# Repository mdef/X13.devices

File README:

The X13.Home project, http://X13Home.org, http://x13home.github.io

X13.devices
===========

Firmware section for project X13.Home

Automation System oriented to "Smart House" over MQTT(SN) protocol

devices     - firmware for Arduino nano (atmega328) nodes and host

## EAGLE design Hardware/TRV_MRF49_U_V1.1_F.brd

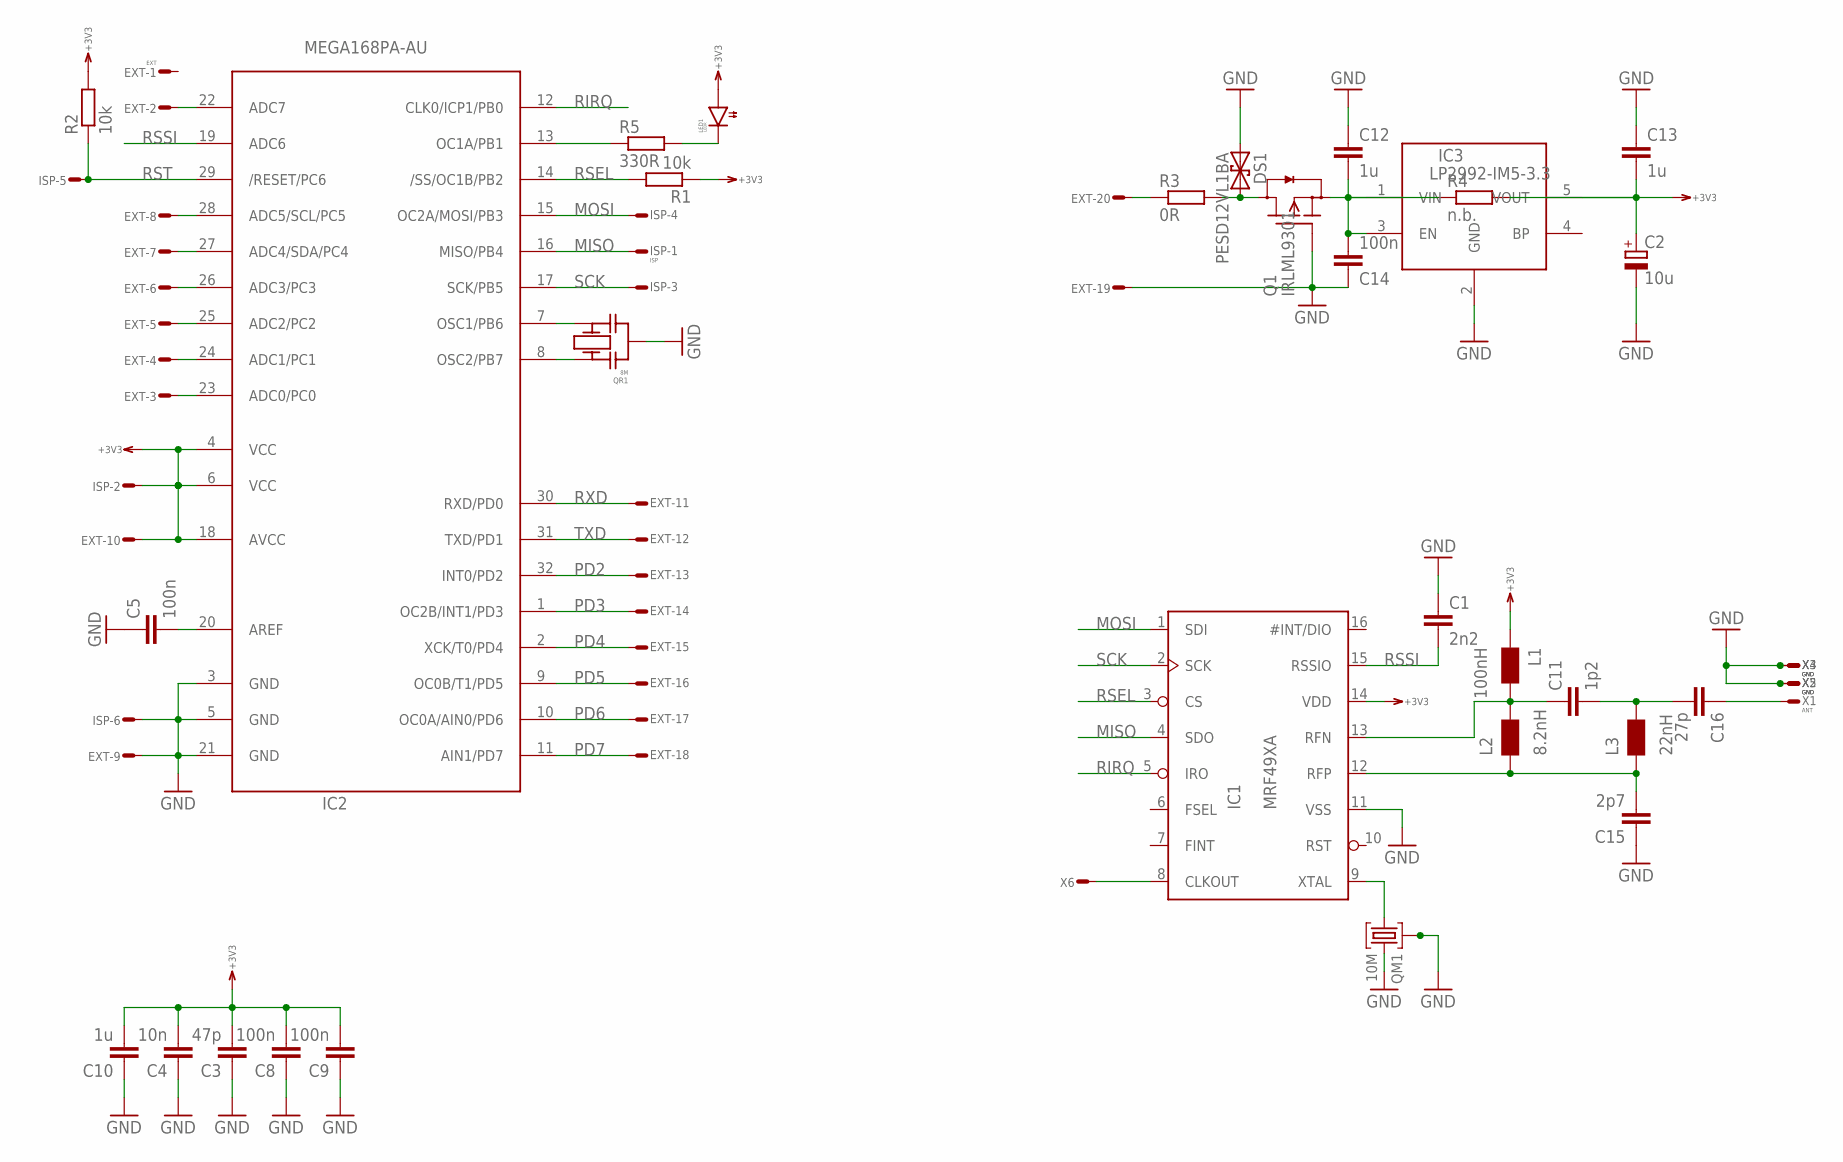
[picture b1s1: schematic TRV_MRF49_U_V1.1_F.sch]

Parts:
C1: 2n2; 0603
C2: 10u; SMC_B
C3: 47p; 0603
C4: 10n; 0603
C5, C8, C9, C14: 100n; 0603
C10, C12, C13: 1u; 0603
C11: 1p2; 0603
C15: 2p7; 0603
C16: 27p; 0603
DS1: PESD12VL1BA; SOD323
EXT: EXT; ML20
IC1: MRF49XA; TSSOP16
IC2: MEGA168PA-AU; TQFP32-08
IC3: LP2992-IM5-3.3; SOT23-5
ISP: ISP; ML6
L1: 100nH; 0603
L2: 8.2nH; 0603
L3: 22nH; 0603
LED1: LEDR; 0603
Q1: IRLML9301; SOT23
QM1: 10M; ABM3C
QR1: 8M; CR
R1, R2: 10k; 0603
R3: 0R; 0603
R4: n.b.; 0603
R5: 330R; 0603
X1: ANT; S2.54/1.27
X2, X3, X4, X5: GND; S2.54/1.27
X6: WIREPADR; S1.27R

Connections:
+3V3: C2.+, C3.2, C4.2, C8.2, C9.2, C10.2, C13.2, EXT.10, IC1.14 (VDD), IC2.4 (VCC), IC2.6 (VCC), IC2.18 (AVCC), IC3.5 (VOUT), ISP.2, L1.1, LED1.1 (A), R1.1, R2.2, R4.2
GND: C1.1, C2.-, C3.1, C4.1, C5.1, C8.1, C9.1, C10.1, C12.1, C13.1, C14.1, C15.1, DS1.A (1), EXT.9, EXT.19, IC1.11 (VSS), IC2.3 (GND), IC2.5 (GND), IC2.21 (GND), IC3.2 (GND), ISP.6, Q1.1 (G), QM1.P$2 (M1), QM1.P$3 (2), QM1.P$4 (M2), QR1.M, X2.1, X3.1, X4.1, X5.1
MISO: IC1.4 (SDO), IC2.16 (MISO/PB4), ISP.1
MOSI: IC1.1 (SDI), IC2.15 (OC2A/MOSI/PB3), ISP.4
unnamed: IC1.8 (CLKOUT), X6.1
unnamed: C11.2, C16.2, L3.2
unnamed: EXT.2, IC2.22 (ADC7)
unnamed: IC1.9 (XTAL), QM1.P$1 (1)
unnamed: DS1.C (2), Q1.3 (D), R3.2
unnamed: C5.2, IC2.20 (AREF)
unnamed: IC2.8 (OSC2/PB7), QR1.1
unnamed: IC2.7 (OSC1/PB6), QR1.2
unnamed: EXT.20, R3.1
unnamed: IC2.13 (OC1A/PB1), R5.1
unnamed: C12.2, C14.2, IC3.1 (VIN), IC3.3 (EN), Q1.2 (S), R4.1
unnamed: C11.1, IC1.13 (RFN), L1.2, L2.2
unnamed: LED1.2 (C), R5.2
unnamed: C15.2, IC1.12 (RFP), L2.1, L3.1
unnamed: C16.1, X1.1
PC0: EXT.3, IC2.23 (ADC0/PC0)
PC1: EXT.4, IC2.24 (ADC1/PC1)
PC2: EXT.5, IC2.25 (ADC2/PC2)
PC3: EXT.6, IC2.26 (ADC3/PC3)
PC4: EXT.7, IC2.27 (ADC4/SDA/PC4)
PC5: EXT.8, IC2.28 (ADC5/SCL/PC5)
PD2: EXT.13, IC2.32 (INT0/PD2)
PD3: EXT.14, IC2.1 (OC2B/INT1/PD3)
PD4: EXT.15, IC2.2 (XCK/T0/PD4)
PD5: EXT.16, IC2.9 (OC0B/T1/PD5)
PD6: EXT.17, IC2.10 (OC0A/AIN0/PD6)
PD7: EXT.18, IC2.11 (AIN1/PD7)
RIRQ: IC1.5 (IRO), IC2.12 (CLK0/ICP1/PB0)
RSEL: IC1.3 (CS), IC2.14 (/SS/OC1B/PB2), R1.2
RSSI: C1.2, IC1.15 (RSSIO), IC2.19 (ADC6)
RST: IC2.29 (/RESET/PC6), ISP.5, R2.1
RXD: EXT.11, IC2.30 (RXD/PD0)
SCK: IC1.2 (SCK), IC2.17 (SCK/PB5), ISP.3
TXD: EXT.12, IC2.31 (TXD/PD1)

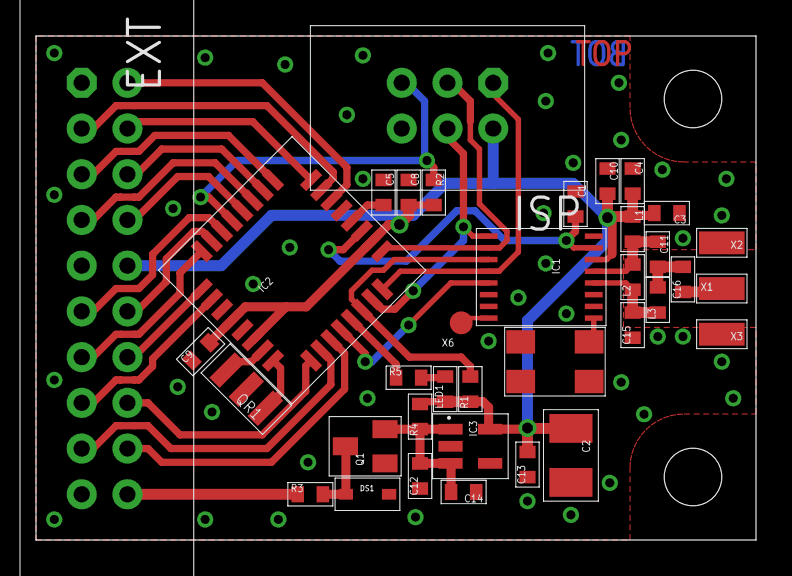
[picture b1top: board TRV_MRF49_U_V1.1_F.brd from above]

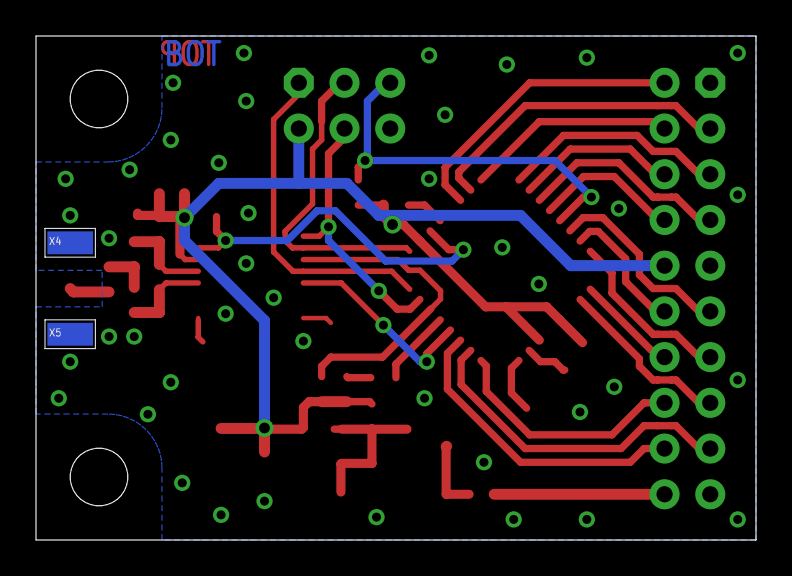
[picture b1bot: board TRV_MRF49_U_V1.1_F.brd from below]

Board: 2 copper layers, 40.0 x 28.0 mm, 38 parts (2 on the bottom side), 38 nets.

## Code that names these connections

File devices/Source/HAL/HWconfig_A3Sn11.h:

/*
Copyright (c) 2011-2014 <comparator@gmx.de>

This file is part of the X13.Home project.
http://X13home.org
http://X13home.net
http://X13home.github.io/

BSD New License
See LICENSE file for license details.
*/

#ifndef HWCONFIG_A3SN11_H
#define HWCONFIG_A3SN11_H

// Busware CSM V2.0
// uc ATMega1284p
// PHY: UART

// PORTA
// PA0  --    LEDG
// PA1  --    LEDR
// PA2  --    R-CFG1.1
// PA3  --    R-CFG1.2
// PA4  CN9
// PA5  CN8
// PA6  --
// PA7  --
// PORTB
// PB0  CN30
// PB1  CN22  RF_IRQ
// PB2  CN24
// PB3  CN25
// PB4  --    RF_NCS
// PB5  CN28  RF_MOSI
// PB6  CN27  RF_MISO
// PB7  CN29  RF_SCK
// PORTC
// PC0  CN15  SCL
// PC1  CN14  SDA
// PC2  CN13  JTAG_TCK
// PC3  CN11  JTAG_TMS
// PC4  CN10  JTAG_TDO
// PC5  CN12  JTAG_TDI
// PC6  --
// PC7  --
// PORTD
// PD0  CN3   RXD0
// PD1  CN4   TXD0
// PD2  CN23  RF_GDO2/Not Used
// PD3  CN6
// PD4  CN7
// PD5  --    R-CFG2
// PD6  --    R-CFG3
// PD7  --

#include <avr/io.h>
#include <avr/eeprom.h>
//#include <util/delay.h>

#include "../../FreeRTOS/include/FreeRTOS.h"
#include "../../FreeRTOS/include/task.h"
#include "../../FreeRTOS/include/queue.h"
#include "../../FreeRTOS/include/semphr.h"

#define INIT_SYSTEM()

// DIO Section
#define DIO_PORT_SIZE               8
#define EXTDIO_MAXPORT_NR           4                                     // Number of digital Ports
#define PORTNUM_2_PORT              {(uint16_t)&PORTA, (uint16_t)&PORTB, (uint16_t)&PORTC, (uint16_t)&PORTD}
#define PORTNUM_2_MASK              {(uint8_t)0x00, (uint8_t)0x00, (uint8_t)0x00, (uint8_t)0x00}
// End DIO Section

// UART Section
#define UART_PORT                   PORTD
#define UART_DDR                    DDRD
#define UART_RX_PIN                 PD0
#define UART_TX_PIN                 PD1
#define UART_RX_DATA                UDR0
#define UART_TX_DATA                UDR0

#define UART_TX_DISABLE_INT()       UCSR0B &= ~(1<<UDRIE0)
#define UART_TX_ENABLE_INT()        UCSR0B |= (1<<UDRIE0)
// End UART Section

#define UART_PHY                    1
#define RF_NODE                     1

#define PHY1_ADDR_t                 uint8_t
#define RF_ADDR_t                   uint8_t
#define ADDR_BROADCAST_PHY1         (PHY1_ADDR_t)0x00
#define ADDR_UNDEF_PHY1             (PHY1_ADDR_t)0xFF
#define ADDR_DEFAULT_RF             (RF_ADDR_t)0x04
#define ADDR_UNDEF_RF               (RF_ADDR_t)0xFF

// Object's Dictionary Section
#define OD_DEV_UC_TYPE              'A'
#define OD_DEV_UC_SUBTYPE           '3'
#define OD_DEV_PHY1                 'S'
#define OD_DEV_PHY2                 'n'
#define OD_DEV_HW_TYP_H             '1'
#define OD_DEV_HW_TYP_L             '1'

#define OD_ADDR_TYPE                objUInt8

#include "../PHY/UART/uart_phy.h"

#define PHY1_Init                   UART_Init
#define PHY1_Send                   UART_Send
#define PHY1_Get                    UART_Get
#define PHY1_NodeId                 objRFNodeId
#define PHY1_GateId                 objGateID
#define UART_ADDR                   phy1
#define UART_ADDR_t                 uint8_t

#define eeprom_init_hw()
#define eeprom_read(pBuf, Addr, Len)  eeprom_read_block((void *)pBuf, (const void *)Addr, (size_t)Len)
#define eeprom_write(pBuf, Addr, Len) eeprom_write_block((const void *)pBuf, (void *)Addr, (size_t)Len)

#endif // HWCONFIG_A3SN11_H

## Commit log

2012-12-31 Public Version.
2012-12-31 Added PDF View
2013-01-05 Development version
2013-01-06 MQTTS.c removed misunderstandings and typing errors extser.c restored delete subroutine
2013-01-21 TWI API changed
2013-01-21 deleted hardware
2013-01-21 New TWI API
2013-01-23 LM75 Prototype
2013-01-29 Merged
2013-02-04 Hih61xx driver untested
2013-02-07 New I2C API, small UART RX changes.
2013-02-07 Version 2.3
2013-02-08 Start OWI
2013-02-08 Start OWI development
2013-02-09 RFM12 aggressive pool method
2013-02-09 Object dictionary changes
2013-02-09 BMP085 Test
2013-02-10 RF aggressive pool method
2013-02-10 Version 2.3a
2013-02-17 Added TWI Bus Status and Watchdog
2013-02-18 TWI Bugfix version
2013-02-19 TWIM Watchdog Version 1.2
2013-02-19 TWI Watchdog
2013-02-20 TWI WatchDog Vers 3
2013-02-21 TWI Watchdog and startup bugfix
2013-02-21 Version 2.4
2013-02-22 Test TWIM WD
2013-02-23 Packed Objects
2013-02-25 Vers 2.4.0
2013-02-25 Version 2.4.0
2013-02-27 Vers 2.4.1
2013-03-01 NOT Working Develop version
2013-03-03 Vers 2.4.2
2013-03-09 Version 2.4.2
2013-03-17 Added Proto Si114x
2013-03-19 Added PROTO RFM23
2013-04-01 LAN Test Version
2013-04-01 Test Version ARP + ICMP + DHCP
2013-04-02 Test3
2013-04-02 Added Node Don't Work
2013-04-02 deleted addr
2013-04-02 little bit
2013-04-03 Alfa Version
2013-04-04 Version 2.5.Alfa
2013-04-04 Alfa 2
2013-04-04 Changed Predefined ID's
2013-04-04 Switch to LAN_RF Added RFM12
2013-04-05 Alfa2
2013-04-05 Alfa 3, LAN Bugfix
2013-04-05 Alfa 4 Version Added PHY's RF - RFM12, configurations UNODE & JNODE
2013-04-05 Alfa 5, Added PHY - CC11xx
2013-04-05 typo
2013-04-14 Optimization
2013-04-15 Changed MQTT and PHY API
2013-04-19 Added PROTO W5100
2013-05-10 Merged RF and LAN Sources
2013-05-10 Proto Version 2.5.0 RF_GATEWAY DON'T WORK
2013-05-11 Gateway don't work
2013-05-11 Added LED LAN Activity Corrected UART-GW API
2013-05-12 Gateway Test Version
2013-05-13 Version 2.5.0.beta1
2013-05-13 RF-GW BugFix
2013-05-14 Compiled with AVR Studio 6.1
2013-05-20 Added panSTamp USE_RTC_OSC = 1
2013-05-21 Version 2.4.3 - Compatibility with Develop version
2013-05-22 Added HEX Files
2013-05-22 Changed MQTTS Proc's Publish, Subscribe, Register Changed Analog inputs configuration Changed RF_USE_RSSI Temporarely unused Added TWI Callback Functions
2013-05-23 Build 2.5.1.b1
2013-05-23 Added HEXs
2013-05-24 Test VArs
2013-05-28 Changed RF API, GW Don't Work !!
2013-05-31 Gateway Work Version
2013-06-04 Si7005 Revision B.
2013-06-05 Version 2.5.2 RC
2013-06-11 Fixed Si7005 Errors
2013-06-14 Change list updated
2013-06-20 Changed Plugins structure
2013-06-25 Added DummyGW device - Gateway w/o RF Interface
2013-06-26 Added BlinkM Prototype
2013-06-27 BlinkM, Pool Version, !! Not Tested
2013-06-27 BlinkM driver work with bus planer.
2013-06-28 Bugfix, Digital IO 19, Added BlinkM TWI Driver, Added Data type Int64
2013-06-30 Added WIZNET prototype
2013-06-30 Added W5200 Register description
2013-07-04 Wiznet HAL
2013-07-20 Wiznet Modi
2013-07-21 Wiznet Added Socket Proto
2013-08-21 Optimize structure
2013-09-04 Added uNode V2.0
2013-09-08 Version 2.5.5 Release Candidate
2013-09-12 Build 2.5.5 RC
2013-10-17 BugFix, Node ADDR = 0xC0 | 0xDB
2013-10-24 BugFix, not stable detection TWI devices
2013-10-25 Updates HEXs
2013-10-30 Readme copy/paste error.
2013-11-11 Added Dummy ATMega256
2013-11-11 Release Version 2.6.0
2013-11-11 Release
2013-11-11 Typo correction
2013-11-12 Added Arduino LAN 16M
2013-11-22 Added TWI Driver CCd2xx[S]
2013-11-28 Added SHT21 proto changed TWI arbitration structure.
2013-11-29 Added TWI Driver MCP23016 Added TWI Driver SHT21 Changed TWI Arbitration
2013-12-01 Connected tested TWI drivers
2013-12-03 Optimized TWI Drivers LM75 and BMP180 Deleted SI7005
2013-12-19 Added Arduino NANO prototype
2014-01-08 Bugfix eeprom.c progmemReadOD fault output state
2014-01-23 Added VERSION
2014-01-28 ExtAI + ExtPWM without PRR
2014-01-30 Don't work
2014-01-30 Added dubug to mqtts
2014-01-30 Tests 2,3,5 Failed
2014-02-05 Debug Version
2014-02-06 Added memory garbage collector, Optimized MQTTS Publish, Subscribe, Register subroutines
2014-02-07 Added DEBUG Information for mqMEM
2014-02-16 Added TWI driver for AM2321
2014-02-20 Added driver prototype for TWI Smart devices
2014-02-20 Smart Proto, HEZ
2014-02-21 Driver for Smart TWI devices, vorked prototype
2014-02-21 TWI driver Smart, optimized version
2014-02-26 Added Smart devices
2014-02-27 ATM_Smart Demo worked version
2014-02-28 Added Smart dimmer, optimization
2014-03-04 Smart Driver RC Version.
2014-03-04 little bit optimized
2014-03-05 !!! DON'T WORK Changed DIO plugin and configuration structure
2014-03-06 Revert to work Version
2014-05-12 Bugfix + Optimization
2014-05-12 Bugfix, Typo Correction
2014-05-12 Incompatible Smart TWI and BlinkM
2014-05-31 Enable analog inputs, configuration error EXTAI_ ->EXTAIN_
2014-06-28 Optimization, Bugfix ADIN, Actualize file-list, typo correction
2014-07-12 Added TWI Drivers from Develop version
2014-08-21 1st public version
2014-08-29 HWconfig__ typo correction, initialisation Timer, disable serial port on delete
2014-08-29 Typo correction, HWconfigDefaultATM.h, Timer Init HWconfigDM_atm256.h correct
2014-09-06 bugfix dio flood, no reaction on flood with another pin on port added eeprom emulation on flash optimization HAL
2014-09-15 Optimized structure added Atmel AVR updated FreeRTOS to 8.2.1
2014-09-24 Added AVR PHY's
2014-10-02 Added,Pseudo random delay between publish retry's Changed Hw config UN,UP, SYSTEM_RESET with WatchDog
2014-10-02 SYSTEM_RESET PS & UN with WatchDog
2014-10-02 Back to the future
2014-10-28 Up/Down Grade from FreeRTOS to "Original" task manager
2014-10-30 Added ATM2560 Optimized Ddevice Info Updated Host
2014-10-31 Added TWI system driver
2014-11-07 Optimized configurations Updated Atmel Device Description file Added Atmel + PWM Changed UART API + HAL for multiport configurations
2014-11-22 Bugfix: mqttsn - underflow buffer on retry with array variables Bugfix: twi - use unallocated memory Bugfix: ARM UART - unhandled exception on HW buffer overflow Added: ENC28J60 DHCP
2014-11-28 Changed UART-PHY Protocol, !! NOT COMPATIBLE WITH OLD VERSIONS Bugfix MQTT-SN premature release publish buffer Bugfix TWI/I2C used unallocated memory Added User Serial port Updated Atmel devices desc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
2014-12-05 improved compatibility with version 3
2014-12-06 Plug-in is now actual
2014-12-08 Updated Atmel device description CC11 now check of chip state
2014-12-09 Added: CC11 Check SPI functioning, and the chip version Changed: F_CPU for atmel moved from project settings to HWconfig_Axxx12.h
2015-03-14 Addem A4En12 to Atmel.xst
2015-03-14 Updated version
2015-03-20 changes to run on arduino nano with cc1101 interface
2015-03-20 arduino nano firmware binary version
2015-03-20 removed all but not firmware
2015-03-20 added description
2015-03-20 corrected files
2015-03-20 added md file with description
2015-03-20 added md file with description to root
2015-03-20 fized links
2015-03-20 updated description
